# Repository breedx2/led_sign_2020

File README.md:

# led_sign_2020

This is a hardware refresh of [a project I started in 1999](https://noisybox.net/electronics/LED_sign).
It involved creating a custom hardware controller for a vintage (1980s) SilentRadio scrolling LED sign.

The previous hardware stack had a Microchip PIC controller with very little RAM.  It was 
hard-wired to a PC via RS232 cable and had zero brains on-device.  The pic allowed the PC
to address and write memory, and the memory was blittled to the sign.

A lot has changed in 20 years.  This is an update.

# update goals

Why update? Because.

* serial port RS232 cable in 2020? Meh.
* Let's try getting on wifi!
* Move more display logic to the device
* eliminate the need for a PC
* make external/remote/iot interfaces easier/fancier.

# hardware

The design is based on an ESP32-DevKitC (generic/ripoff with ipex antenna connector).  It uses 
4 2-channel high current (4A) MAXIM drivers for the rows. Wifi is achieved with a panel mount antenna
(because the case is steel). A high-current 5V power supply powers the sign and the ESP32 devkit.

# bom

tbd

# notes

tbd

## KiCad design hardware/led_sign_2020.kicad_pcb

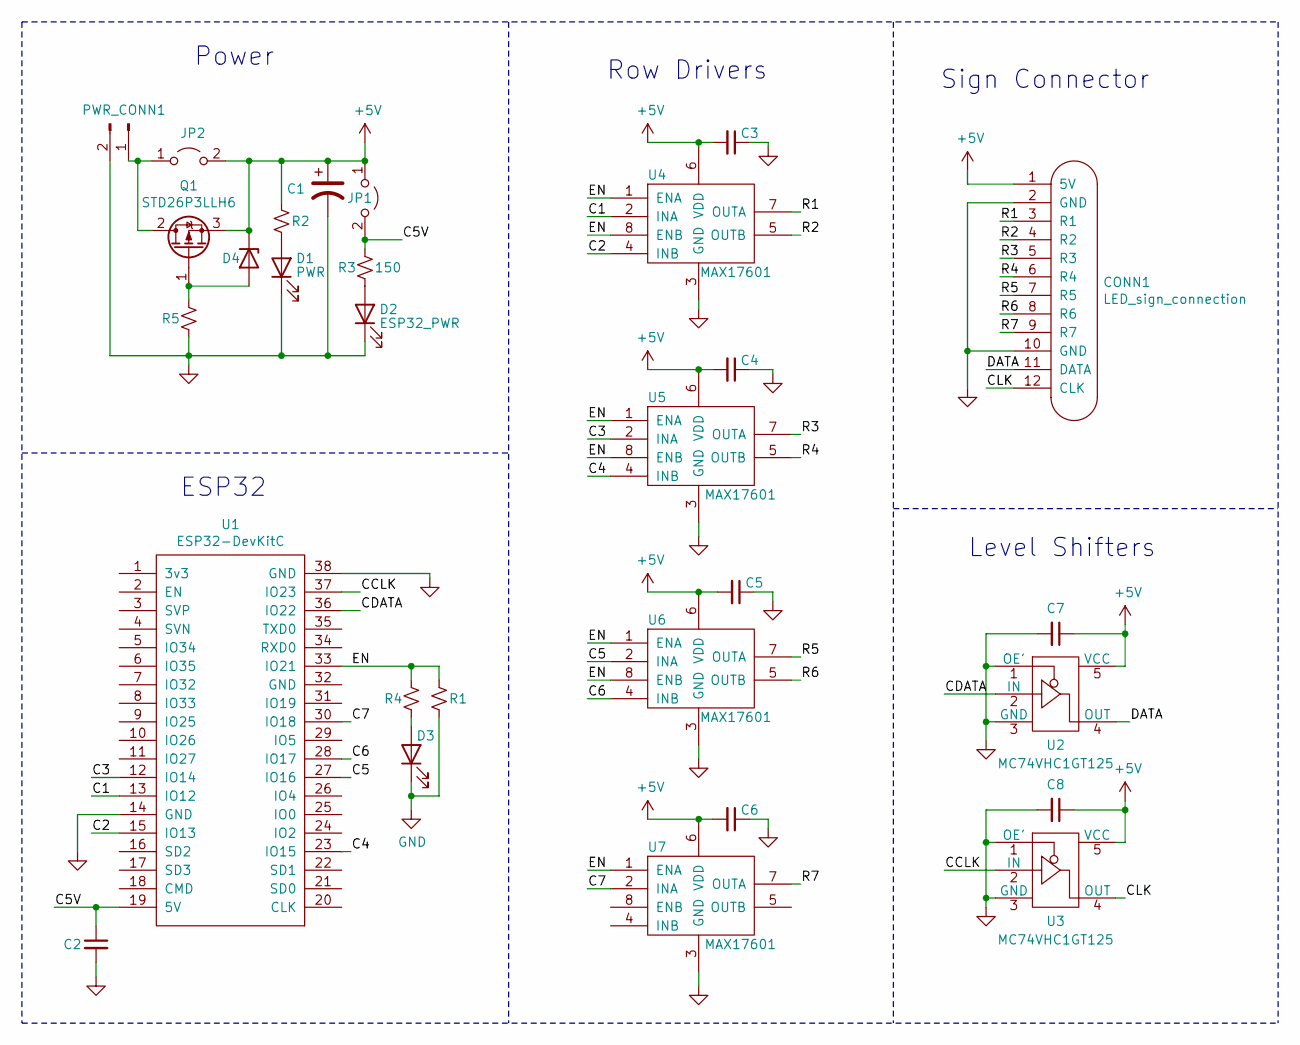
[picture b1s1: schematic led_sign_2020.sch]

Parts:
C1: CP1; CP_Radial_D10.0mm_P5.00mm
C2, C3, C4, C5, C6, C7, C8: 0.1uF; C_0805_2012Metric
CONN1: LED_sign_connection; JST_XH_B12B-XH-A_1x12_P2.50mm_Vertical
D1: PWR; LED_0805_2012Metric
D2: ESP32_PWR; LED_0805_2012Metric
D3: LED; LED_0805_2012Metric
D4: D_Zener; D_SOD-123
JP1: ESP32_5V; PinHeader_1x02_P2.54mm_Vertical
JP2: prot_short; PinHeader_1x02_P2.54mm_Vertical
PWR_CONN1: Conn_01x02_Male; JST_XH_B2B-XH-A_1x02_P2.50mm_Vertical
Q1: STD26P3LLH6; TO-252-3_TabPin2
R1: 4.7k; R_0805_2012Metric
R2, R3: 150; R_0805_2012Metric
R4: 68ohm; R_0805_2012Metric
R5: 100k; R_0805_2012Metric
U1: ESP32-DevKitC; ESP32-DevKitC-DIP-38
U2, U3: MC74VHC1GT125; TSOP-5_1.65x3.05mm_P0.95mm
U4, U5, U6, U7: MAX17601; SO-8_3.9x4.9mm_P1.27mm

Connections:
+5V: C1.1, C3.2, C4.2, C5.2, C6.2, C7.1, C8.1, CONN1.1 (5V), D4.1 (K), JP1.1 (A), JP2.2 (B), Q1.3 (S), R2.2, U2.5 (VCC), U3.5 (VCC), U4.6 (VDD), U5.6 (VDD), U6.6 (VDD), U7.6 (VDD); also elsewhere on the board
/C1: U1.13 (IO12), U4.2 (INA)
/C2: U1.15 (IO13), U4.4 (INB)
/C3: U1.12 (IO14), U5.2 (INA)
/C4: U1.23 (IO15), U5.4 (INB)
/C5: U1.27 (IO16), U6.2 (INA)
/C5V: C2.1, JP1.2 (B), R3.2, U1.19 (5V)
/C6: U1.28 (IO17), U6.4 (INB)
/C7: U1.30 (IO18), U7.2 (INA)
/CCLK: U1.37 (IO23), U3.2 (IN)
/CDATA: U1.36 (IO22), U2.2 (IN)
/CLK: CONN1.12 (CLK), U3.4 (OUT)
/DATA: CONN1.11 (DATA), U2.4 (OUT)
/EN: R1.2, R4.2, U1.33 (IO21), U4.1 (ENA), U4.8 (ENB), U5.1 (ENA), U5.8 (ENB), U6.1 (ENA), U6.8 (ENB), U7.1 (ENA)
/R1: CONN1.3 (R1), U4.7 (OUTA)
/R2: CONN1.4 (R2), U4.5 (OUTB)
/R3: CONN1.5 (R3), U5.7 (OUTA)
/R4: CONN1.6 (R4), U5.5 (OUTB)
/R5: CONN1.7 (R5), U6.7 (OUTA)
/R6: CONN1.8 (R6), U6.5 (OUTB)
/R7: CONN1.9 (R7), U7.7 (OUTA)
GND: C1.2, C2.2, C3.1, C4.1, C5.1, C6.1, C7.2, C8.2, CONN1.2 (GND), CONN1.10 (GND), D1.1 (K), D2.1 (K), D3.1 (K), PWR_CONN1.2, R1.1, R5.1, U1.14 (GND), U1.38 (GND), U2.1 (OE'), U2.3 (GND), U3.1 (OE'), U3.3 (GND), U4.3 (GND), U5.3 (GND), U6.3 (GND), U7.3 (GND); also elsewhere on the board
unnamed: D1.2 (A), R2.1
unnamed: D2.2 (A), R3.1
unnamed: D3.2 (A), R4.1
unnamed: D4.2 (A), Q1.1 (G), R5.2
unnamed: JP2.1 (A), PWR_CONN1.1, Q1.2 (D)

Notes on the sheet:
Power
ESP32
Sign Connector
Level Shifters
Row Drivers

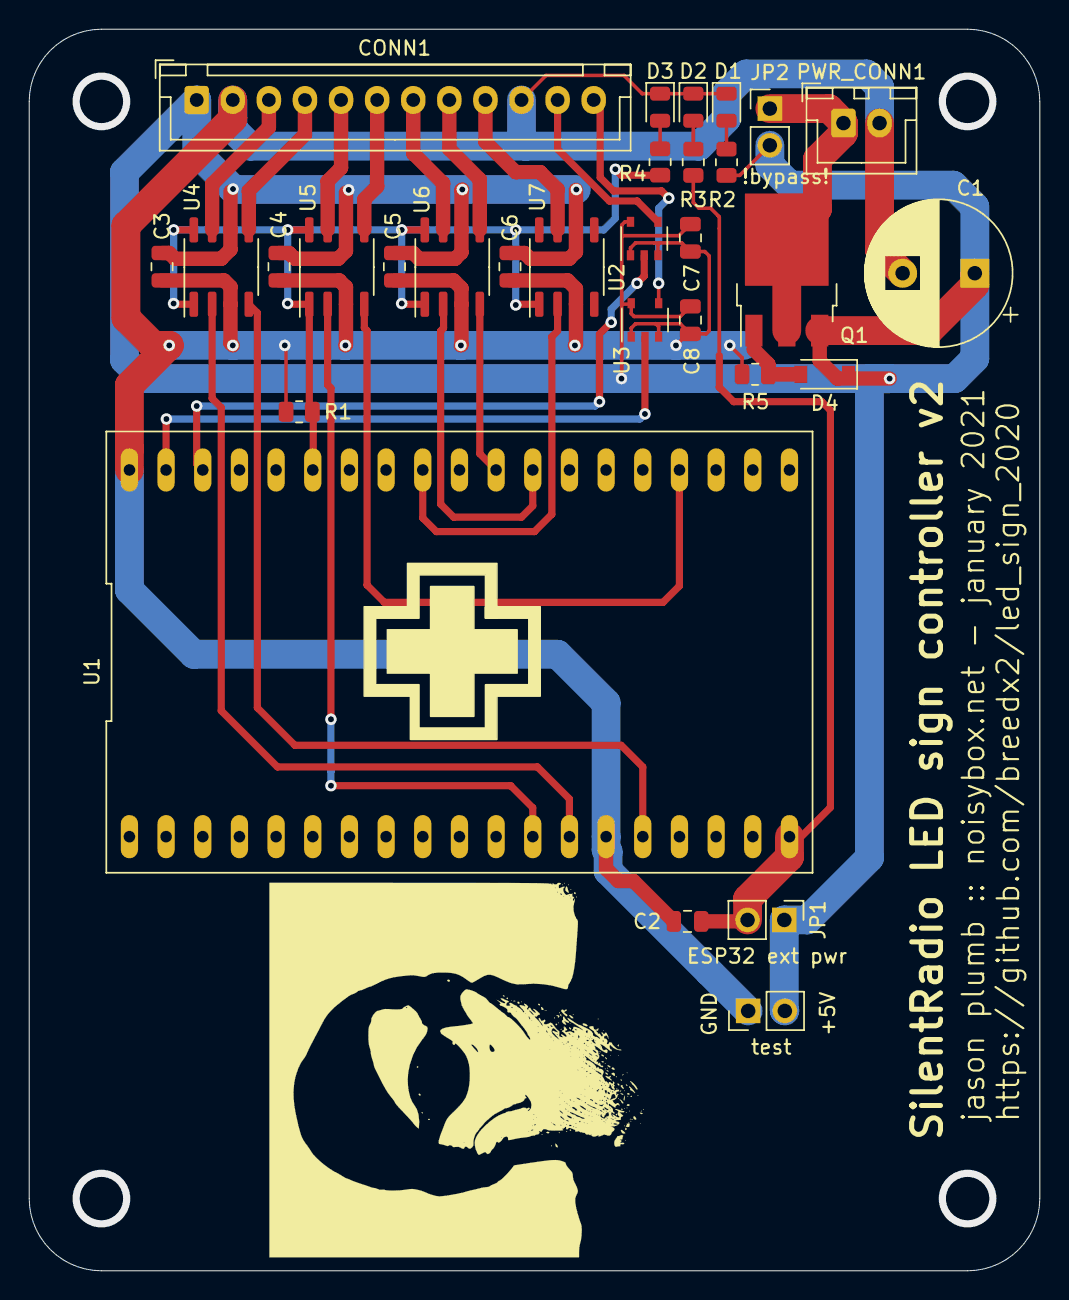
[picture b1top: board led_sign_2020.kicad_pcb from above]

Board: 2 copper layers, 70.0 x 86.0 mm, 30 parts (0 on the bottom side), 27 nets.

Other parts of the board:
test: PinHeader_1x02_P2.54mm_Vertical

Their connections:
+5V: test.2; also elsewhere on the board
GND: test.1; also elsewhere on the board

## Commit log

2021-01-04 initial import
2021-01-04 change enable lines to be pulled down and microcontrolled. light up when enabled.
2021-01-04 add power LEDs
2021-01-04 annotate
2021-01-04 assign footprints
2021-01-06 add updated svg
2021-01-07 add reverse polarity protection
2021-01-10 all kinds of reorg and netlabels
2021-01-11 associate footprint
2021-01-13 footprints
2021-01-13 routing pcb
2021-01-17 board layout
2021-01-17 fix stray net
2021-01-17 beef up those power busses
2021-01-19 reroute in progress
2021-01-19 routed
2021-01-19 tweaks
2021-01-20 no idea what I changed
2021-01-20 settings
2021-01-20 fix zener footprint
2021-01-21 footprint
2021-01-21 add rediculous avatar and boost readme
2021-01-21 update image
2021-01-26 add test point and silk notes
2021-01-26 visibility
2021-01-26 get silk off top pad derp
2021-01-26 ugly trace
2021-01-28 scratching at software
2021-01-28 wait for wifi to connect
2021-01-29 add sign state
2021-01-30 move sign_state to simply sign and add invert and rot
2021-01-30 roll up and down
2021-01-30 start printing text on the sign
2021-02-01 print left, center, or right aligned
2021-04-22 more sign abstraction
2021-04-22 project update
2021-04-25 add pin mappings
2021-04-25 more hardware work
2021-04-25 fix bug
2021-04-25 add update script
2021-04-25 add sign updater
2021-04-25 various fixes and updates (wip)
2021-04-25 wip with refresh rate issues. going to spi
2021-04-25 work in progress (getting spi going)
2021-04-25 mostly working spi (still slow)
2021-04-25 more troubleshooting speed
2021-05-03 wip commit before changing to row-based model
2021-05-06 row based sign memory, work in progress
2021-05-06 working on column toggle on
2021-05-06 cleanup and fixes
2021-05-06 build out for every row
2021-05-09 fix rot_right
2021-05-09 add shift right
2021-05-09 refactor
2021-05-09 implement left functions too
2021-05-09 cleanup
2021-05-09 implement roll up and down
2021-05-10 all the unbinding
2021-05-10 fixes
2021-05-10 break out useful test reduce copy/paste fatigue
2021-05-10 fix up main so sign is healthy on boot
2021-05-10 well this test shows the problem...
2021-05-12 a custom build from tip to try, will iterate
2021-05-12 try pinning to core 1
2021-05-12 update firmware
2021-05-12 new firmware
2021-05-13 sign memory
2021-05-13 rename for clarity
2021-05-14 add test files too why not
2021-05-16 starting some commands
2021-05-16 make a string
2021-05-16 add get_col to sign
2021-05-16 comment about kerning
2021-05-16 implement crid
2021-05-17 refactor commonality in crid/criu
2021-05-17 implement mwoo
2021-05-17 implement mwoi
2021-05-17 implement sr
2021-05-17 implement sl
2021-05-18 implement rou and rod
2021-05-18 work in progress for rolling lines with content in (rid)
2021-05-18 dedupe code
2021-05-18 implement rid and riu
2021-05-18 add mwc
2021-05-18 dont waste time sleeping on empty columns
2021-05-19 fix out of bounds in blit and add tests
2021-05-19 implement lwipe
2021-05-19 implement rwipe
2021-05-19 implement strobe
2021-05-19 fix bug in wipes. add direction to criu/crid
2021-05-19 implement sil and sir
2021-05-19 add rando and lib for shuffle
2021-05-19 implement randi and randt
2021-05-26 implement dump
2021-05-26 implement kriu
2021-05-26 implement krid
2021-05-26 refactor for reuse
2021-05-28 implement roll krod and krou
2021-05-28 it's a laser beam, bozo. follow it, it's a surprise
2021-05-28 first msl before trying to save memory/ram
2021-05-28 add note about mem usage
2021-05-28 implement msr
2021-05-29 add throbber command
2021-05-29 work in progress
2021-05-29 add test4
2021-05-29 work in progress to limit allocations
2021-05-29 right and left prints dont allocate
2021-05-29 crid/criu dont allocate now
2021-05-29 krod/krou/krid/kriu no longer allocate
2021-05-29 lazr no longer allocates
2021-05-29 lwipe doesn't allocate memory now. also removed local vars named "len" because they're evil.
2021-05-29 rwipe doesnt allocate memory now
2021-05-29 msl and msr no longer allocate giant column buffers
2021-05-29 randt no longer preallocates buffer
2021-05-29 rid no longer allocates screen buff
2021-05-29 riu no longer allocates
2021-05-29 remove depreated allocating methods
2021-05-29 whoops fix bug
2021-05-29 beef up test
2021-05-29 fix spacing bug and remove semi
2021-05-30 initial attempts
2021-06-13 cut and run from this work in progress. probably ditching python for now
2021-06-13 move old python stuff out of the way
2021-06-14 setup for arduino
2021-06-14 setup
2021-06-14 add submodule
2021-06-14 setting it up...and it seems to work
2021-06-14 setting up arduino build
2021-06-16 firing up the sign hardware
2021-06-16 it blinks
2021-07-01 change mode
2021-07-01 update sdk
2021-07-01 update arduino sources
2021-07-01 update main to test two methods of timers
2021-07-01 set frequency to 240
2021-07-01 sign memory functions
2021-07-01 timer based sign refresher
2021-07-01 add new sources
2021-07-01 display simple pattern
2021-07-01 little fx tweak
2021-07-06 add a font and omg paint a G
2021-07-06 add Sign object
2021-07-06 add column offsets
2021-07-06 add blit
2021-07-06 starting on the sign printer
2021-07-06 add printer
2021-07-06 implement center and cleanups
2021-07-06 add sign::invert
2021-07-06 start sign commands
2021-07-07 get the time printing
2021-07-11 delegation and spreading clear around
2021-07-11 fix bug in print and add ctr
2021-07-11 add reverser
2021-07-11 add utils
2021-07-11 add crid
2021-07-11 test crid right and fix reverse bug
2021-07-11 add criu
2021-07-11 refactor to reduce duplication
2021-07-11 bug fix
2021-07-11 change tick rate to get ms resolution for delays
2021-07-11 add memory dump helper
2021-07-11 slow SPI a little for reliability and demo code
2021-07-11 clenaup
2021-07-12 implement rod and crwipe
2021-07-12 implement rou
2021-07-12 implement sign on/off methods
2021-07-12 implement rid
2021-07-12 implement riu
2021-07-12 demo!
2021-07-12 demo tweak
2021-07-13 add mwoi
2021-07-13 add lwipe
2021-07-14 slow down spi again for reliability and enhance demo
2021-07-14 add sil
2021-07-14 add sir
2021-07-18 implement rando
2021-07-18 add randi()
2021-07-18 add lazr()
2021-07-24 add krid and kriu
2021-07-24 add krod() and krou()
2021-07-25 add msl/msr
2021-07-25 test fin
2021-07-26 move demo into its own unit
2021-07-26 stub command parser and build serial command reader
2021-07-26 starting command parsing
2021-07-29 more command parsing work
2021-07-29 parse crid/criu with params
2021-07-29 add demo to main and add throb and parser for throb
2021-07-29 parse ctr
2021-07-29 add invert parse and kr** parse
2021-07-29 add parser for lazr and left
2021-07-29 parse common string + speed commands
2021-07-31 parse commands that just take single speed arg
2021-07-31 parse sir and sil
2021-07-31 bring krid/kriu/krod/krou parsing into the common delcarative fold
2021-07-31 parse on/off
2021-07-31 parse strobe
2021-07-31 parser for right command
2021-07-31 change getString to non-regex because it can blow the stack
2021-08-01 factor out tuple range finder for string portion
2021-08-01 add parseDigits and remove usage of firstMatchGroup
2021-08-01 add afterString, afterDigits, and afterWhitespace
2021-08-01 remove firstMatchGroup
2021-08-01 swizzle ctr to not use regex
2021-08-04 change throb parsing to not use regex
2021-08-04 change parseTwo to not use reges and remove parseNum that used ssub_match
2021-08-04 remove all regex now
2021-08-04 add dump command
2021-08-04 scratching around on wifi
2021-08-04 first stub of server component
2021-08-04 add a little ntp action
2021-08-08 add control socket
2021-08-08 making progress on websocket
2021-08-08 auth stage and progressing with dump
2021-08-09 remote dump works
2021-08-09 fixing up dump
2021-08-14 hacking a web presence
2021-09-05 websocket and ui progress
2021-09-08 parse command from the wire, and support length into char *
2021-09-08 working on paint mode
2021-09-08 painting work
2021-09-09 adding some widge
2021-09-09 eraser
2021-09-15 guis are hard -- cover more state changes and consistent icon state
2021-09-15 add rin command
2021-09-15 a little faster plz
2021-09-15 send live typing
2021-09-29 better splash
2021-09-29 incremental ui improvements
